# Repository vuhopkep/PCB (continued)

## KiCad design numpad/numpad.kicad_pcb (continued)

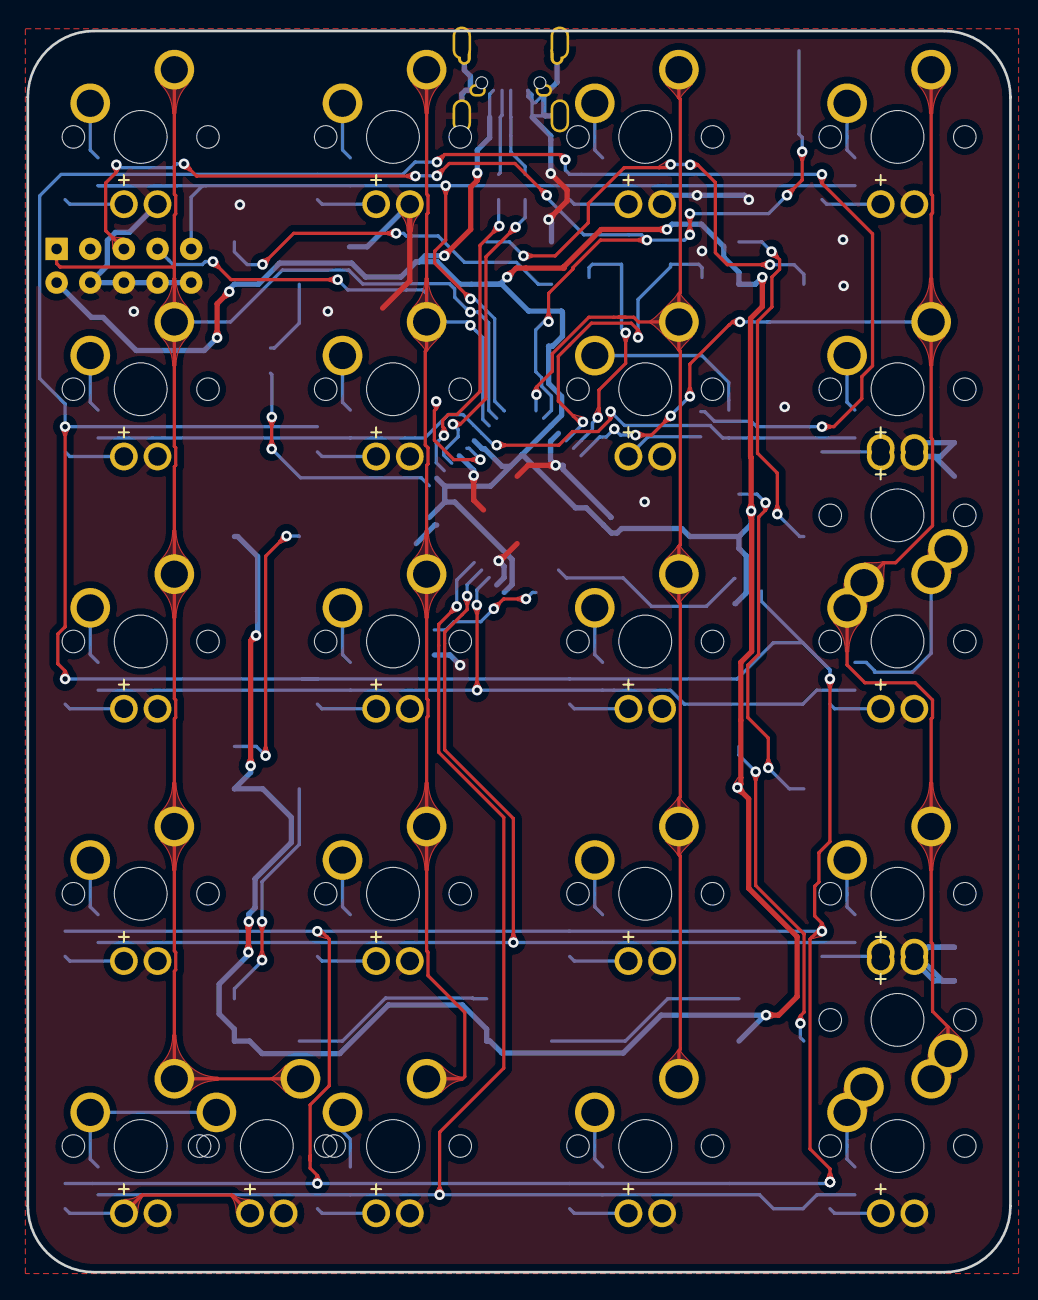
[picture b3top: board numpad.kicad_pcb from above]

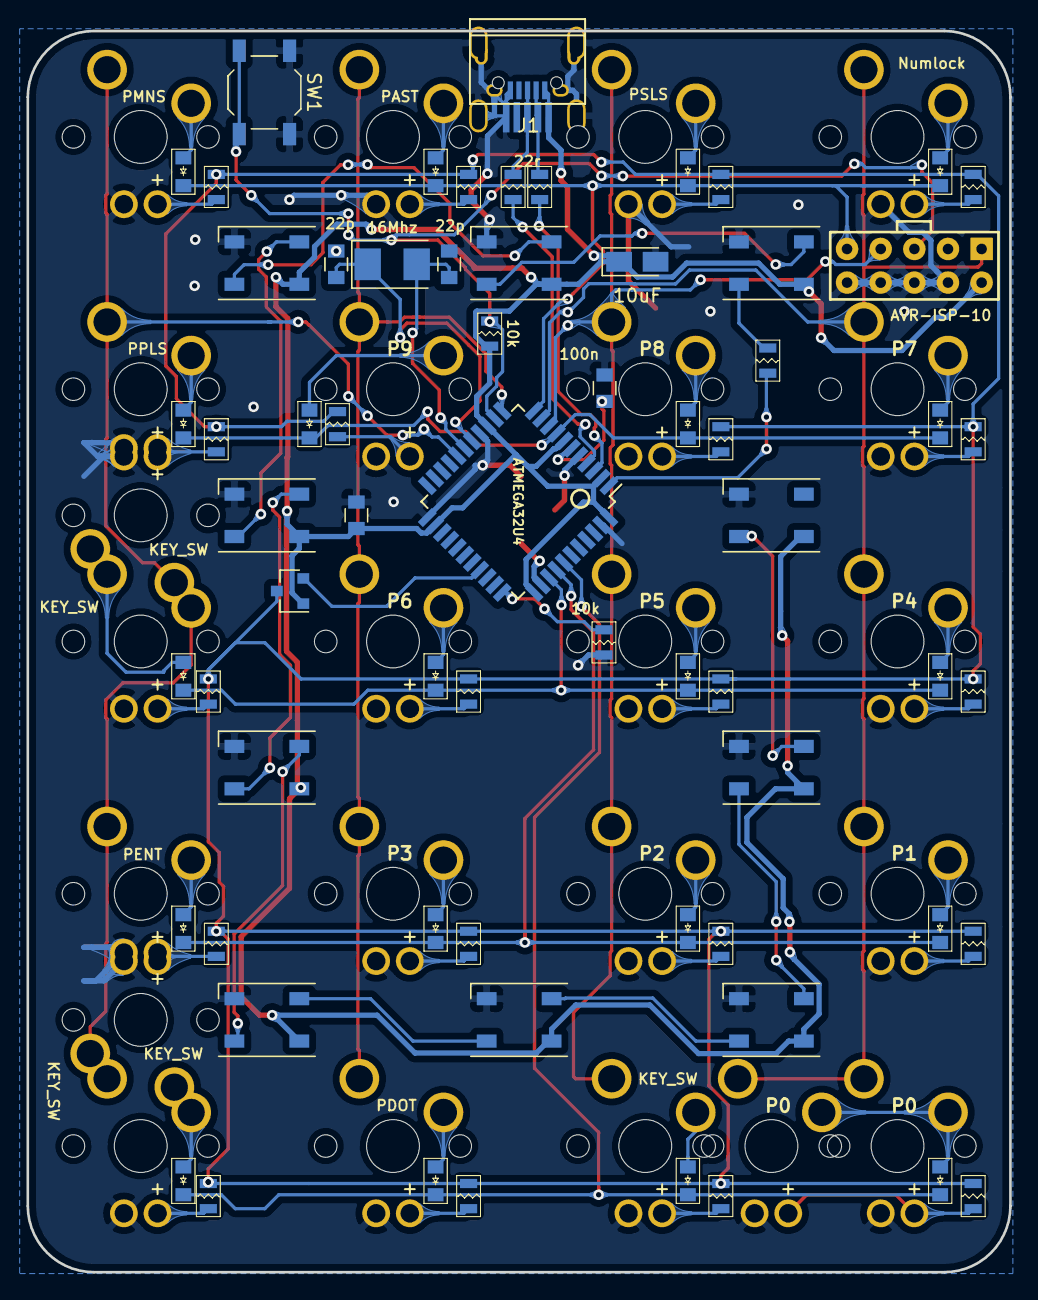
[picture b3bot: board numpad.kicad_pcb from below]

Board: 2 copper layers, 74.2 x 93.7 mm, 113 parts (67 on the bottom side), 73 nets.

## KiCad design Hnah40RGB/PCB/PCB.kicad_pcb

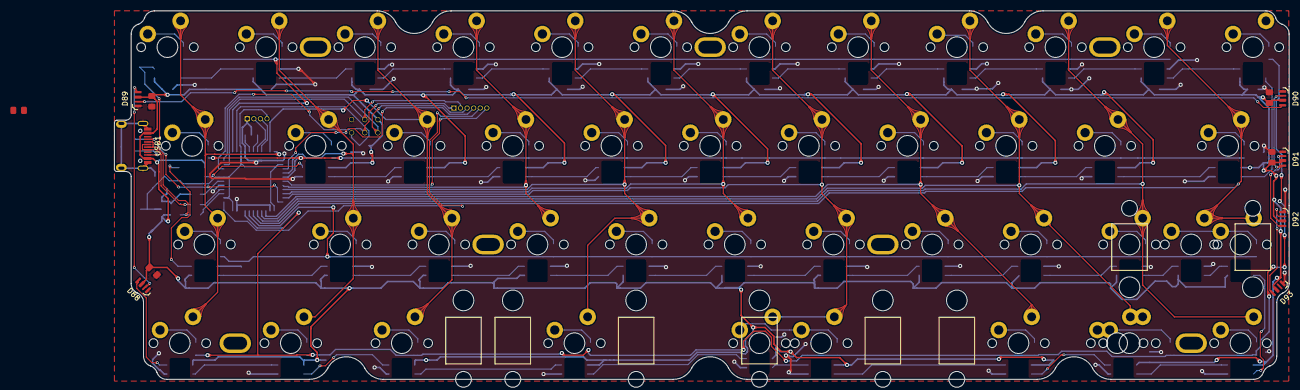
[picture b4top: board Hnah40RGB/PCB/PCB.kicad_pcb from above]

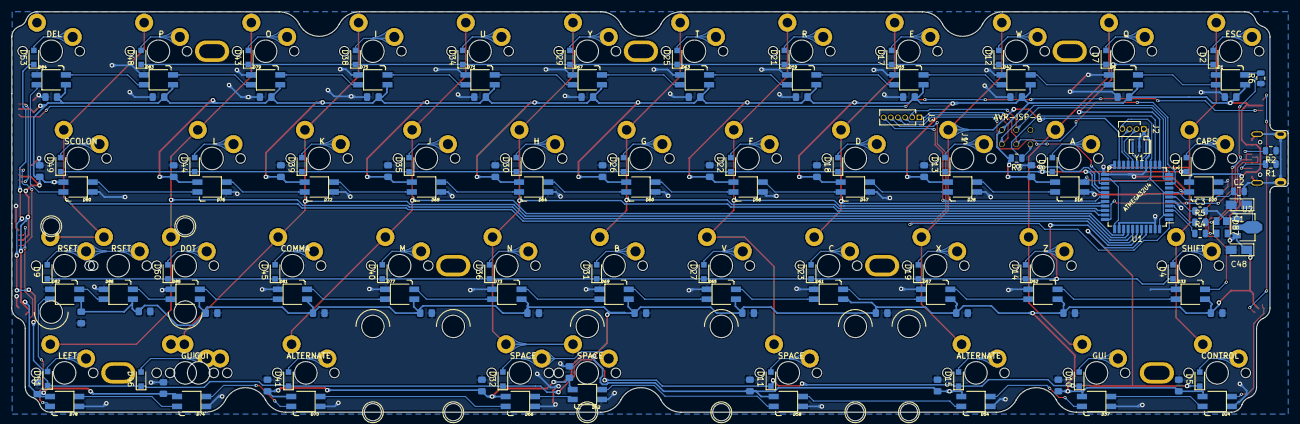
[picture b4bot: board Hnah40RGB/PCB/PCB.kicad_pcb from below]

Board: 2 copper layers, 226.8 x 71.1 mm, 218 parts (146 on the bottom side), 128 nets.

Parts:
C1, C48: 106; CP_Tantalum_3216
C2, C3: 105; C_0805_2012Metric
C4, C5, C6, C7, C8, C9, C10, C11, C12, C13, C14, C15, C16, C17, C18, C19, C20, C21, C22, C23, C24, C25, C26, C27, C28, C29, C30, C31, C32, C33, C34, C35, C36, C37, C38, C39, C40, C41, C42, C43, C44, C45, C46, C47, C49, C50, C51, C52: 104; C_0805
D1, D6, D16, D20, D24, D28, D33, D37, D42, D47, D52, D54, D55, D56, D57, D58, D59, D60, D61, D62, D63, D64, D65, D66, D67, D68, D69, D70, D71, D72, D73, D74, D75, D76, D77, D78, D79, D80, D81, D82, D83, D84, D85, D86: SK6812MINI; LED_SK6812-3535_Backlight
D2, D3, D4, D5, D7, D8, D9, D10, D11, D12, D13, D14, D15, D17, D18, D19, D21, D22, D23, D25, D26, D27, D29, D30, D31, D32, D34, D35, D36, D38, D39, D40, D41, D43, D44, D45, D46, D48, D49, D50, D51, D53: 4148; D_SOD-323_HandSoldering
D87: PRTR5V0U2X; SOT-143
D88, D89, D90, D91, D92, D93: SK6805; SK6805-4020
H1, H3, H5, H7, H9, H10, H12: Screw; Poker_oval_hole
H2, H8, H11, H13, H14, H15, H16, H17: Stablilizer; Cherry_Stab_PCBMounted
J1: AVR-ISP-6; AVR_ISP_6
J2: Conn_01x04_Female; PinSocket_1x04_P1.27mm_Vertical
J3: Conn_01x06_Female; PinSocket_1x06_P1.27mm_Vertical
R1, R2: 5k1; R_0805_2012Metric
R3, R6: 10k; R_0805_2012Metric
R4, R5: 22R; R_0805_2012Metric
SW1, SW3, SW34: SPACE; CHERRY_PCB_100H_Thermal
SW2: ESC; CHERRY_PCB_100H_Thermal
SW4: CAPS; CHERRY_PCB_100H_Thermal
SW5, SW11: RSFT; CHERRY_PCB_100H_Thermal
SW6: SHIFT; CHERRY_PCB_100H_Thermal
SW7: CONTROL; CHERRY_PCB_100H_Thermal
SW8, SW12, SW49: GUI; CHERRY_PCB_100H_Thermal
SW9: Q; CHERRY_PCB_100H_Thermal
SW10: A; CHERRY_PCB_100H_Thermal
SW14: W; CHERRY_PCB_100H_Thermal
SW15: S; CHERRY_PCB_100H_Thermal
SW16: Z; CHERRY_PCB_100H_Thermal
SW17, SW43: ALTERNATE; CHERRY_PCB_100H_Thermal
SW19: E; CHERRY_PCB_100H_Thermal
SW20: D; CHERRY_PCB_100H_Thermal
SW21: X; CHERRY_PCB_100H_Thermal
SW23: R; CHERRY_PCB_100H_Thermal
SW24: F; CHERRY_PCB_100H_Thermal
SW25: C; CHERRY_PCB_100H_Thermal
SW27: T; CHERRY_PCB_100H_Thermal
SW28: G; CHERRY_PCB_100H_Thermal
SW29: V; CHERRY_PCB_100H_Thermal
SW31: Y; CHERRY_PCB_100H_Thermal
SW32: H; CHERRY_PCB_100H_Thermal
SW33: B; CHERRY_PCB_100H_Thermal
SW36: U; CHERRY_PCB_100H_Thermal
SW37: J; CHERRY_PCB_100H_Thermal
SW38: N; CHERRY_PCB_100H_Thermal
SW40: I; CHERRY_PCB_100H_Thermal
SW41: K; CHERRY_PCB_100H_Thermal
SW42: M; CHERRY_PCB_100H_Thermal
SW46: O; CHERRY_PCB_100H_Thermal
SW47: L; CHERRY_PCB_100H_Thermal
SW48: COMMA; CHERRY_PCB_100H_Thermal
SW52: P; CHERRY_PCB_100H_Thermal
SW53: SCOLON; CHERRY_PCB_100H_Thermal
SW54: DOT; CHERRY_PCB_100H_Thermal
SW55: LEFT; CHERRY_PCB_100H_Thermal
SW57: DEL; CHERRY_PCB_100H_Thermal
U1: ATMEGA32U4; TQFP-44_Pitch0.8mm
U2: AP1117-50; SOT-89-3
USB1: HRO-TYPE-C-31-M-12
Y1: 16MHz; Resonator_SMD_muRata_CSTxExxV-3Pin_3.0x1.1mm

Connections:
+5V: C1.1, C2.1, J2.4, U1.2, U1.7, U1.14, U1.24, U1.34, U1.44, U2.2
/B1: J1.3, J3.1, U1.9
/B2: J1.4, J3.2, U1.10
/B3: J1.1, J3.3, U1.11
/B4: J3.6, U1.28
/Col1-layout1: SW2.2, SW4.2, SW6.2, SW7.2, U1.22
/Col2-layout1: SW9.2, SW10.2, SW12.2, SW16.2, U1.26
/Col3-layout1: SW14.2, SW15.2, SW17.2, SW21.2, U1.21
/Col4-layout1: SW19.2, SW20.2, SW25.2, U1.29
/Col5-layout1: SW1.2, SW23.2, SW24.2, SW29.2, U1.30
/Col6-layout1: SW27.2, SW28.2, SW33.2, U1.31
/Col7-layout1: SW3.2, SW31.2, SW32.2, SW34.2, SW38.2, U1.32
/Col8-layout1: SW36.2, SW37.2, SW42.2, SW43.2, U1.36
/Col9-layout1: SW40.2, SW41.2, SW48.2, SW49.2, U1.37
/Col10-layout1: SW46.2, SW47.2, SW54.2, SW55.2, U1.38
/Col11-layout1: SW5.2, SW11.2, SW52.2, SW53.2, U1.39
/D4: J3.4, U1.25
/D+: D87.2, R5.2, USB1.6, USB1.8
/D-: D87.3, R4.2, USB1.5, USB1.7
/E6: J3.5, U1.1
/RGB-layout1: D1.3, R6.2, U1.33
/Reset: J1.5, R3.1, U1.13
/row1-layout1: D2.1, D7.1, D12.1, D17.1, D21.1, D25.1, D29.1, D34.1, D38.1, D43.1, D48.1, U1.12
/row2-layout1: D3.1, D8.1, D13.1, D18.1, D22.1, D26.1, D30.1, D35.1, D39.1, D44.1, D49.1, U1.27
/row3-layout1: D4.1, D9.1, D14.1, D19.1, D23.1, D27.1, D31.1, D36.1, D40.1, D45.1, D50.1, U1.40
/row4-layout1: D5.1, D10.1, D11.1, D15.1, D32.1, D41.1, D46.1, D51.1, D53.1, U1.41
GND: C1.2, C2.2, C3.2, C4.2, C5.2, C6.2, C7.2, C8.2, C9.2, C10.2, C11.2, C12.2, C13.2, C14.2, C15.2, C16.2, C17.2, C18.2, C19.2, C20.2, C21.2, C22.2, C23.2, C24.2, C25.2, C26.2, C27.2, C28.2, C29.2, C30.2, C31.2, C32.2, C33.2, C34.2, C35.2, C36.2, C37.2, C38.2, C39.2, C40.2, C41.2, C42.2, C43.2, C44.2, C45.2, C46.2, C47.2, C48.2, C49.2, C50.2, C51.2, C52.2, D1.2, D6.2, D16.2, D20.2, D24.2, D28.2, D33.2, D37.2, D42.2, D47.2, D52.2, D54.2, D55.2, D56.2, D57.2, D58.2, D59.2, D60.2, D61.2, D62.2, D63.2, D64.2, D65.2, D66.2, D67.2, D68.2, D69.2, D70.2, D71.2, D72.2, D73.2, D74.2, D75.2, D76.2, D77.2, D78.2, D79.2, D80.2, D81.2, D82.2, D83.2, D84.2, D85.2, D86.2, D87.1, D88.2, D89.2, D90.2, D91.2, D92.2, D93.2, J1.6, J2.1, R1.1, R2.1, R6.1, U1.5, U1.15, U1.23, U1.35, U1.43, U2.1, USB1.1, USB1.12, USB1.13, Y1.2
unnamed: C3.1, U1.6
unnamed: D1.1, D6.3
unnamed: D2.2, SW2.1
unnamed: D3.2, SW4.1
unnamed: D4.2, SW6.1
unnamed: D5.2, SW7.1
unnamed: D7.2, SW9.1
unnamed: D8.2, SW10.1
unnamed: D9.2, SW5.1, SW11.1
unnamed: D10.2, SW12.1
unnamed: D11.2, SW1.1
unnamed: D12.2, SW14.1
unnamed: D13.2, SW15.1
unnamed: D14.2, SW16.1
unnamed: D15.2, SW17.1
unnamed: D16.1, D20.3
unnamed: D16.3, D28.1
unnamed: D17.2, SW19.1
unnamed: D18.2, SW20.1
unnamed: D19.2, SW21.1
unnamed: D20.1, D33.3
unnamed: D21.2, SW23.1
unnamed: D22.2, SW24.1
unnamed: D23.2, SW25.1
unnamed: D24.1, D88.3
unnamed: D24.3, D37.1
unnamed: D25.2, SW27.1
unnamed: D26.2, SW28.1
unnamed: D27.2, SW29.1
unnamed: D28.3, D47.1
unnamed: D29.2, SW31.1
unnamed: D30.2, SW32.1
unnamed: D31.2, SW33.1
unnamed: D32.2, SW3.1, SW34.1
unnamed: D33.1, D52.3
unnamed: D34.2, SW36.1
unnamed: D35.2, SW37.1
unnamed: D36.2, SW38.1
unnamed: D37.3, D54.1
unnamed: D38.2, SW40.1
unnamed: D39.2, SW41.1
unnamed: D40.2, SW42.1
unnamed: D41.2, SW43.1
unnamed: D42.1, D55.3
unnamed: D6.1, D42.3
unnamed: D43.2, SW46.1
unnamed: D44.2, SW47.1
unnamed: D45.2, SW48.1
unnamed: D46.2, SW8.1, SW49.1
unnamed: D47.3, D56.1
unnamed: D48.2, SW52.1
unnamed: D49.2, SW53.1
unnamed: D50.2, SW54.1
unnamed: D51.2, SW55.1
unnamed: D52.1, D57.3
unnamed: D53.2, SW57.1
unnamed: D54.3, D58.1
unnamed: D55.1, D59.3
unnamed: D56.3, D60.1
unnamed: D57.1, D61.3
unnamed: D58.3, D62.1
unnamed: D59.1, D63.3
unnamed: D60.3, D64.1
unnamed: D61.1, D65.3
unnamed: D62.3, D66.1
unnamed: D63.1, D67.3
unnamed: D64.3, D68.1
unnamed: D65.1, D69.3
unnamed: D66.3, D70.1
unnamed: D67.1, D71.3
unnamed: D68.3, D72.1
unnamed: D69.1, D73.3
unnamed: D70.3, D74.1
unnamed: D71.1, D75.3
unnamed: D72.3, D76.1
unnamed: D73.1, D77.3
unnamed: D74.3, D78.1
unnamed: D75.1, D79.3
unnamed: D76.3, D80.1
unnamed: D77.1, D81.3
unnamed: D78.3, D82.1
unnamed: D79.1, D83.3
unnamed: D80.3, D84.1
unnamed: D81.1, D85.3
unnamed: D82.3, D86.1
unnamed: D83.1, D84.3
unnamed: D85.1, D86.3
unnamed: D88.1, D89.3
unnamed: D89.1, D90.3
unnamed: D90.1, D91.3
unnamed: D91.1, D92.3
unnamed: D92.1, D93.3
unnamed: J2.2, U1.18
unnamed: J2.3, U1.19
unnamed: R1.2, USB1.10
unnamed: R2.2, USB1.4
unnamed: R4.1, U1.3
unnamed: R5.1, U1.4
unnamed: U1.16, Y1.1
unnamed: U1.17, Y1.3
VCC: C4.1, C5.1, C6.1, C7.1, C8.1, C9.1, C10.1, C11.1, C12.1, C13.1, C14.1, C15.1, C16.1, C17.1, C18.1, C19.1, C20.1, C21.1, C22.1, C23.1, C24.1, C25.1, C26.1, C27.1, C28.1, C29.1, C30.1, C31.1, C32.1, C33.1, C34.1, C35.1, C36.1, C37.1, C38.1, C39.1, C40.1, C41.1, C42.1, C43.1, C44.1, C45.1, C46.1, C47.1, C48.1, C49.1, C50.1, C51.1, C52.1, D1.4, D6.4, D16.4, D20.4, D24.4, D28.4, D33.4, D37.4, D42.4, D47.4, D52.4, D54.4, D55.4, D56.4, D57.4, D58.4, D59.4, D60.4, D61.4, D62.4, D63.4, D64.4, D65.4, D66.4, D67.4, D68.4, D69.4, D70.4, D71.4, D72.4, D73.4, D74.4, D75.4, D76.4, D77.4, D78.4, D79.4, D80.4, D81.4, D82.4, D83.4, D84.4, D85.4, D86.4, D87.4, D88.4, D89.4, D90.4, D91.4, D92.4, D93.4, J1.2, R3.2, U2.3, USB1.2, USB1.11

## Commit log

2019-05-27 Hnah40V1
2019-05-27 Hpah
2019-05-27 update gerber file and refill ground
2019-08-05 Watermark update
2019-08-17 Tải lên Numpad RGB (Chưa chạy thử)
    Upload numpad rgb có thể ghép với nhau tạo thành phím ortholiner 40%.
    Sử dụng vi điều khiển atmega32u4, giao tiếp usb typeC 2.0, led nền rgb từng phím sk6812-3535, có loa, jump chờ giao tiếp i2c, uart.
2019-08-17 sửa lại bản vẽ nguyên lý
2019-09-11 missing wire fix
2019-09-11 add new keyboard Hnah40rgb
